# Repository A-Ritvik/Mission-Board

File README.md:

# The Mission Board
The mission board is a robotics control board with space for up to 8 motors and 4 servos featuring both ESP32 and RP2040 processors at its core. It also has a display to achieve easier debugging and customization. Sensors include a gyro, accelerometer, and magnetometer. 

# 3D Renders/Images
With Case (PS. Image is slightly off)-

PCB -

# Full Feature List

- Gyro, Accelerometer, Magnetometer
- Up to 4 servos
- Up to 8 motors
- Display connector
- 2 USB for programming RP2040 and ESP32 (no power functionality)
- 1 Barrel Jack for power
- Debug Lights + 5 Customizable Switches

# Case

The case uses a bottom and top part; the bottom part holds the pcb while the top part holds the display. The top part is removable and uses 2 4M screws to attach, and the bottom part needs 3 6M screws to attach to the PCB. 

# Schematic & PCB

# Bill of Materials

The full BOM can be found under the productions folder in CSV format. The total comes to around 132.22$ to produce the board.

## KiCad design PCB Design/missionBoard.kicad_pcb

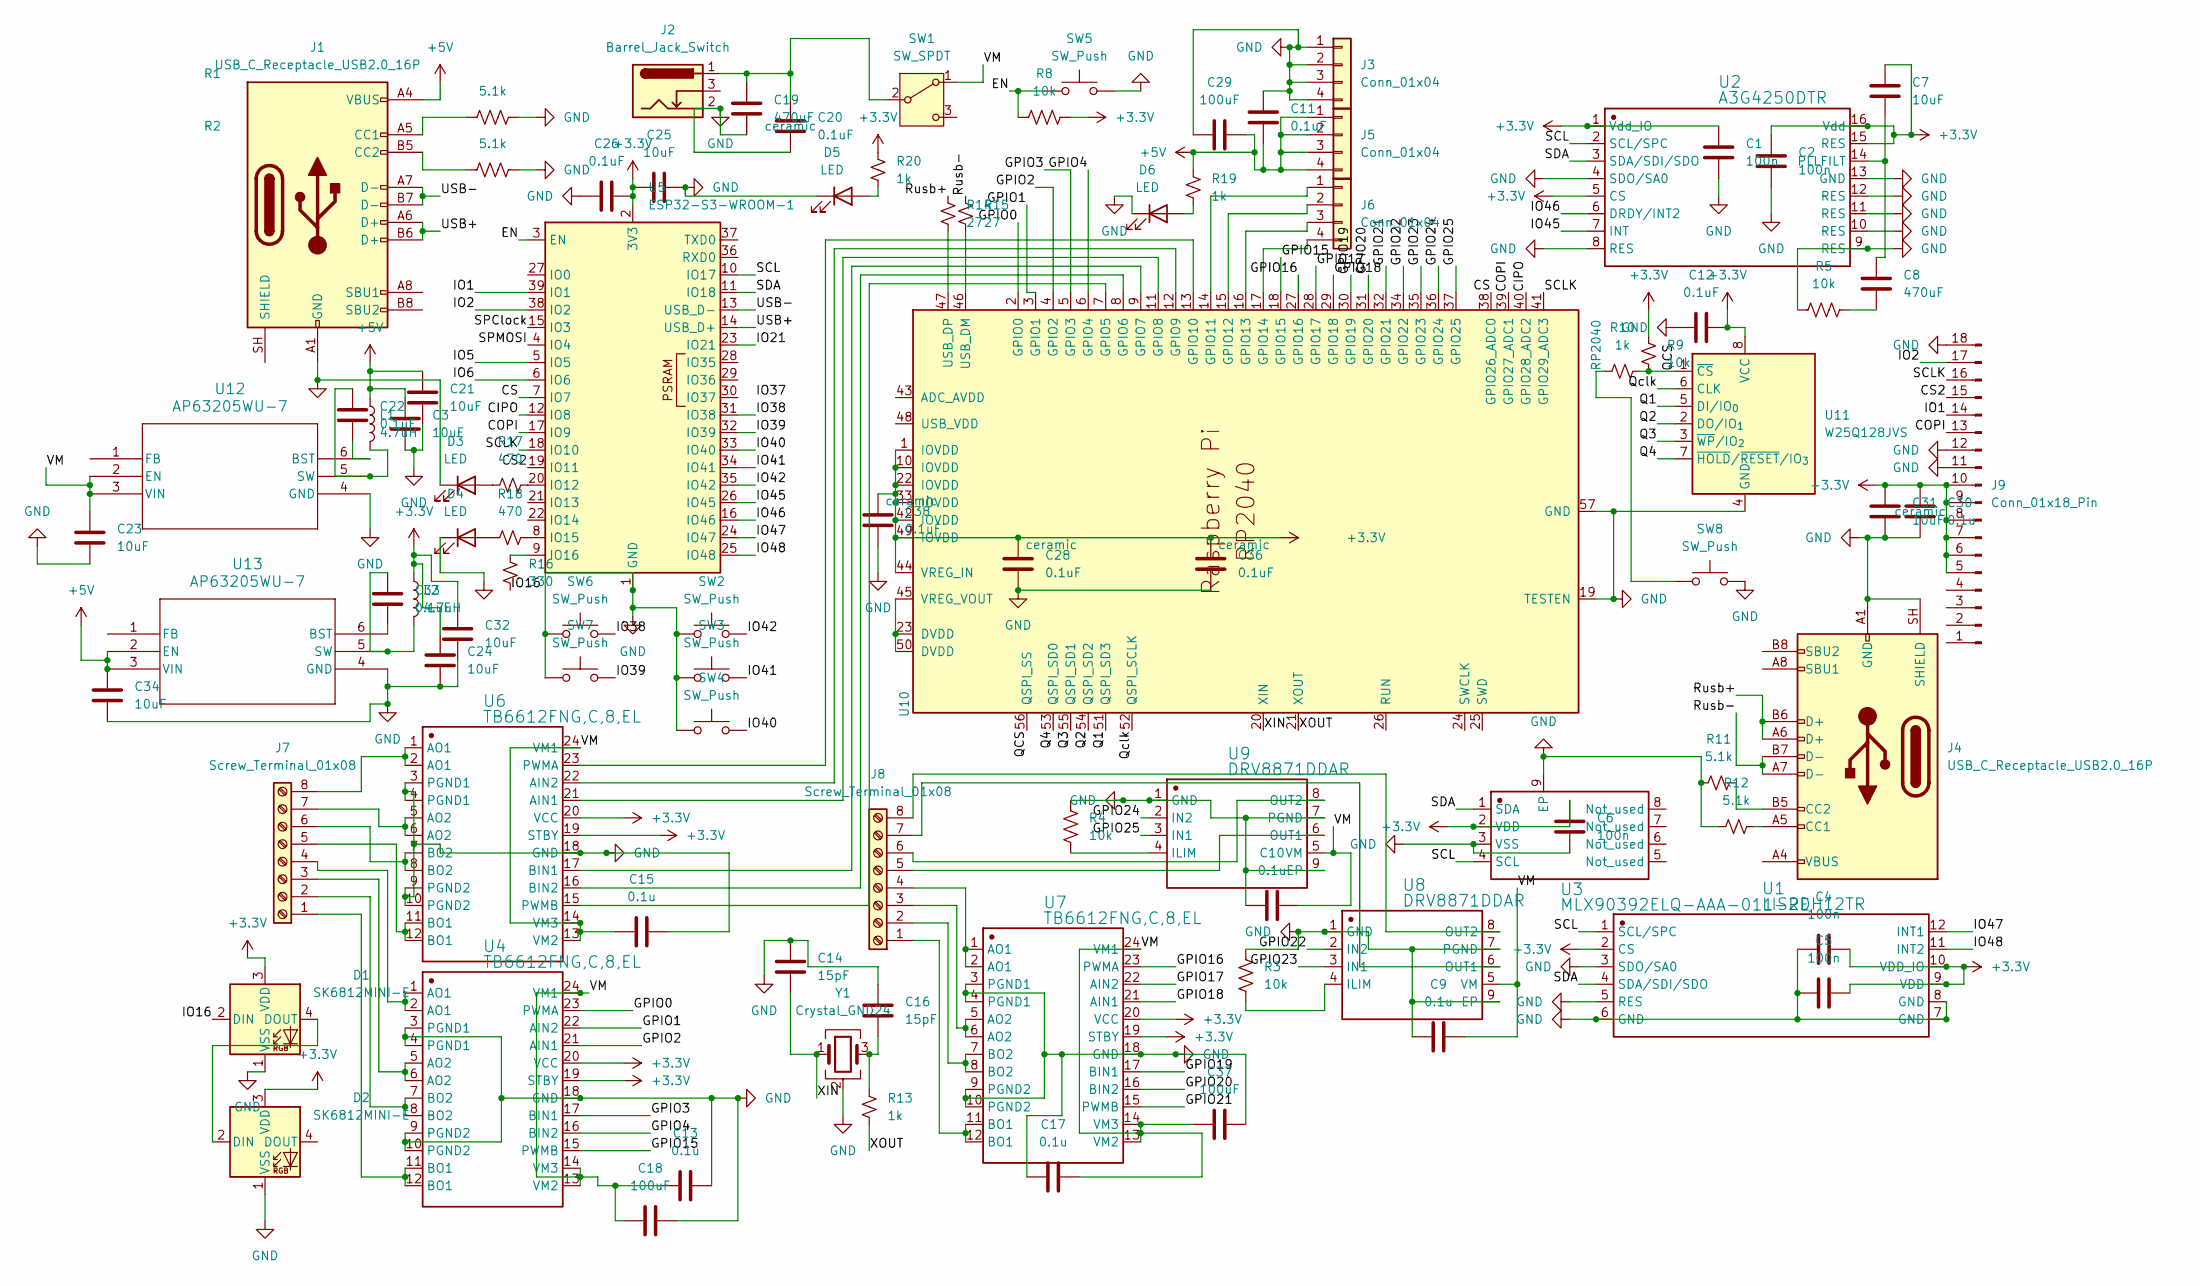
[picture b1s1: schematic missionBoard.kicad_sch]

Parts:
C1, C2, C4, C5, C6: 100n; C_0402_1005Metric
C3, C7, C21, C23, C24, C25, C31, C32, C34: 10uF; C_0402_1005Metric
C8, C19: 470uF; C_Elec_10x10.2
C9, C10, C13, C15, C17, C30: 0.1u; C_0402_1005Metric
C11, C12, C20, C22, C26, C28, C33, C36, C38: 0.1uF; C_0402_1005Metric
C14, C16: 15pF; C_0603_1608Metric
C18, C29, C37: 100uF; C_Elec_6.3x7.7
D1, D2: SK6812MINI-E; LED_SK6812MINI-E_3.2x2.8mm_P1.5mm_ReverseMount
D3, D4, D5, D6: LED; LED_0603_1608Metric
J1, J4: USB_C_Receptacle_USB2.0_16P; USB_C_Receptacle_HCTL_HC-TYPE-C-16P-01A
J2: Barrel_Jack_Switch; BarrelJack_Kycon_KLDX-0202-xC_Horizontal
J3, J5, J6: Conn_01x04; PinHeader_1x04_P2.54mm_Vertical
J7, J8: Screw_Terminal_01x08; TerminalBlock_Phoenix_MKDS-3-8-5.08_1x08_P5.08mm_Horizontal
J9: Conn_01x18_Pin; Hirose_FH12-18S-0.5SH_1x18-1MP_P0.50mm_Horizontal
L1, L2: 4.7uH; L_APV_ANR4030
R1, R2, R11, R12: 5.1k; R_0402_1005Metric
R3, R4, R5, R8, R9: 10k; R_0402_1005Metric
R10, R13: 1k; R_0402_1005Metric
R14, R15: 27; R_0402_1005Metric
R16: 330; R_0603_1608Metric
R17, R18: 470; R_0603_1608Metric
R19, R20: 1k; R_0603_1608Metric
SW1: SW_SPDT; SW_SPDT_Shouhan_MSK12C02
SW2, SW3, SW4, SW6, SW7: SW_Push; SW_SPST_SKQG_WithoutStem
SW5, SW8: SW_Push; SW_Push_SPST_NO_Alps_SKRK
U1: LIS2DH12TR; SENSOR_LIS2DH12; Manufacturer Part LIS2DH12TR
U2: A3G4250DTR; Manufacturer Part A3G4250DTR
U3: MLX90392ELQ-AAA-011-RE; UTDFN-8 2x2.5_MEL; Manufacturer Part MLX90392ELQ-AAA-011-RE
U4, U6, U7: TB6612FNG,C,8,EL; SOP65P760X160-24N; Manufacturer Part TB6612FNG,C,8,EL
U5: ESP32-S3-WROOM-1
U8, U9: DRV8871DDAR; VREG_LM5017MR_NOPB; Manufacturer Part DRV8871DDAR
U10: RP2040; RP2040-QFN-56
U11: W25Q128JVS; SOIC-8_5.3x5.3mm_P1.27mm
U12, U13: AP63205WU-7; SOIC_05WU-7_DIO
Y1: Crystal_GND24; Crystal_SMD_3225-4Pin_3.2x2.5mm

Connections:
+3.3V: C1.1, C2.1, C4.2, C5.2, C6.1, C7.1, C12.1, C24.1, C25.1, C26.2, C28.2, C30.1, C31.2, C32.1, C36.2, C38.2, D1.3 (VDD), D2.3 (VDD), J9.5, J9.6, J9.7, J9.8, J9.9, J9.10, L2.1, R8.2, R9.1, R20.1, U1.2 (CS), U1.9 (VDD), U1.10 (VDD_IO), U2.1 (Vdd_IO), U2.5 (CS), U2.15 (RES), U2.16 (Vdd), U3.2 (VDD), U4.19 (STBY), U4.20 (VCC), U5.2 (3V3), U6.19 (STBY), U6.20 (VCC), U7.19 (STBY), U7.20 (VCC), U10.1 (IOVDD), U10.10 (IOVDD), U10.22 (IOVDD), U10.33 (IOVDD), U10.42 (IOVDD), U10.44 (VREG_IN), U10.49 (IOVDD), U11.8 (VCC)
+5V: C3.1, C11.2, C21.1, C29.1, C34.1, J1.A4 (VBUS), J1.A9 (VBUS), J1.B4 (VBUS), J1.B9 (VBUS), J5.1, J5.2, J5.3, J5.4, L1.1, R19.1, U13.2 (EN), U13.3 (VIN)
/CIPO: U5.12 (IO8), U10.40 (GPIO28_ADC2)
/COPI: J9.13, U5.17 (IO9), U10.39 (GPIO27_ADC1)
/CS: U5.7 (IO7), U10.38 (GPIO26_ADC0)
/CS2: J9.15, U5.19 (IO11)
/EN: R8.1, SW5.1, U5.3 (EN)
/GPIO0: U4.23 (PWMA), U10.2 (GPIO0)
/GPIO1: U4.22 (AIN2), U10.3 (GPIO1)
/GPIO2: U4.21 (AIN1), U10.4 (GPIO2)
/GPIO3: U4.17 (BIN1), U10.5 (GPIO3)
/GPIO4: U4.16 (BIN2), U10.6 (GPIO4)
/GPIO15: U4.15 (PWMB), U10.18 (GPIO15)
/GPIO16: U7.23 (PWMA), U10.27 (GPIO16)
/GPIO17: U7.22 (AIN2), U10.28 (GPIO17)
/GPIO18: U7.21 (AIN1), U10.29 (GPIO18)
/GPIO19: U7.17 (BIN1), U10.30 (GPIO19)
/GPIO20: U7.16 (BIN2), U10.31 (GPIO20)
/GPIO21: U7.15 (PWMB), U10.32 (GPIO21)
/GPIO22: U8.2 (IN2), U10.34 (GPIO22)
/GPIO23: U8.3 (IN1), U10.35 (GPIO23)
/GPIO24: U9.2 (IN2), U10.36 (GPIO24)
/GPIO25: U9.3 (IN1), U10.37 (GPIO25)
/IO1: J9.14, U5.39 (IO1)
/IO2: J9.17, U5.38 (IO2)
/IO5: U5.5 (IO5)
/IO6: U5.6 (IO6)
/IO16: D1.2 (DIN), R16.2
/IO21: U5.23 (IO21)
/IO38: SW6.2, U5.31 (IO38)
/IO39: SW7.2, U5.32 (IO39)
/IO40: SW4.2, U5.33 (IO40)
/IO41: SW3.2, U5.34 (IO41)
/IO42: SW2.2, U5.35 (IO42)
/IO45: U2.7 (INT), U5.26 (IO45)
/IO46: U2.6 (DRDY/INT2), U5.16 (IO46)
/IO47: U1.12 (INT1), U5.24 (IO47)
/IO48: U1.11 (INT2), U5.25 (IO48)
/Q1: U10.51 (QSPI_SD3), U11.5 (DI/IO_{0})
/Q2: U10.54 (QSPI_SD2), U11.2 (DO/IO_{1})
/Q3: U10.55 (QSPI_SD1), U11.3 (~WP/IO_{2})
/Q4: U10.53 (QSPI_SD0), U11.7 (~HOLD/~RESET/IO_{3})
/QCS: R9.2, R10.2, U10.56 (QSPI_SS), U11.1 (~CS)
/Qclk: U10.52 (QSPI_SCLK), U11.6 (CLK)
/Rusb+: J4.A6 (D+), J4.B6 (D+), R14.1
/Rusb-: J4.A7 (D-), J4.B7 (D-), R15.1
/SCL: U1.1 (SCL/SPC), U2.2 (SCL/SPC), U3.4 (SCL), U5.10 (IO17)
/SCLK: J9.16, U5.18 (IO10), U10.41 (GPIO29_ADC3)
/SDA: U1.4 (SDA/SDI/SDO), U2.3 (SDA/SDI/SDO), U3.1 (SDA), U5.11 (IO18)
/SPClock: U5.15 (IO3)
/SPMOSI: U5.4 (IO4)
/USB+: J1.A6 (D+), J1.B6 (D+), U5.14 (USB_D+)
/USB-: J1.A7 (D-), J1.B7 (D-), U5.13 (USB_D-)
/VM: C9.1, C10.1, C13.2, C15.2, C17.1, C18.1, C23.1, C37.1, SW1.1 (A), U4.13 (VM2), U4.14 (VM3), U4.24 (VM1), U6.13 (VM2), U6.14 (VM3), U6.24 (VM1), U7.13 (VM2), U7.14 (VM3), U7.24 (VM1), U8.5 (VM), U9.5 (VM), U12.2 (EN), U12.3 (VIN)
/XIN: C14.2, U10.20 (XIN), Y1.1
/XOUT: R13.2, U10.21 (XOUT)
GND: C1.2, C2.2, C3.2, C4.1, C5.1, C6.2, C9.2, C10.2, C11.1, C12.2, C13.1, C14.1, C15.1, C16.1, C17.2, C18.2, C19.2, C20.1, C21.2, C23.2, C24.2, C25.2, C26.1, C28.1, C29.2, C30.2, C31.1, C32.2, C34.2, C36.1, C37.2, C38.1, D1.1 (VSS), D2.1 (VSS), D3.1 (K), D4.1 (K), D5.1 (K), D6.1 (K), J1.A1 (GND), J1.A12 (GND), J1.B1 (GND), J1.B12 (GND), J2.2, J3.1, J3.2, J3.3, J3.4, J4.A1 (GND), J4.A12 (GND), J4.B1 (GND), J4.B12 (GND), J4.SH (SHIELD), J9.11, J9.12, J9.18, R1.2, R2.2, R3.2, R4.2, R5.1, R11.1, R12.1, SW2.1, SW3.1, SW4.1, SW5.2, SW6.1, SW7.1, SW8.2, U1.3 (SDO/SA0), U1.5 (RES), U1.6 (GND), U1.7 (GND), U1.8 (GND), U2.4 (SDO/SA0), U2.8 (RES), U2.9 (RES), U2.10 (RES), U2.11 (RES), U2.12 (RES), U2.13 (GND), U3.3 (VSS), U3.9 (EP), U4.3 (PGND1), U4.4 (PGND1), U4.9 (PGND2), U4.10 (PGND2), U4.18 (GND), U5.1 (GND), U5.40 (GND), U5.41 (GND), U6.3 (PGND1), U6.4 (PGND1), U6.9 (PGND2), U6.10 (PGND2), U6.18 (GND), U7.3 (PGND1), U7.4 (PGND1), U7.9 (PGND2), U7.10 (PGND2), U7.18 (GND), U8.1 (GND), U8.7 (PGND), U8.9 (EP), U9.1 (GND), U9.7 (PGND), U9.9 (EP), U10.19 (TESTEN), U10.57 (GND), U11.4 (GND), U12.4 (GND), U13.4 (GND), Y1.2 (G), Y1.4 (G)
unnamed: C8.2, R5.2
unnamed: C16.2, R13.1, Y1.3
unnamed: D1.4 (DOUT), D2.2 (DIN)
unnamed: D3.2 (A), R17.1
unnamed: D4.2 (A), R18.1
unnamed: D5.2 (A), R20.2
unnamed: D6.2 (A), R19.2
unnamed: J1.A5 (CC1), R1.1
unnamed: J1.B5 (CC2), R2.1
unnamed: J4.A5 (CC1), R12.2
unnamed: J4.B5 (CC2), R11.2
unnamed: J4.A4 (VBUS), J4.A9 (VBUS), J4.B4 (VBUS), J4.B9 (VBUS)
unnamed: J6.1, U10.14 (GPIO11)
unnamed: J6.2, U10.15 (GPIO12)
unnamed: J6.3, U10.16 (GPIO13)
unnamed: J6.4, U10.17 (GPIO14)
unnamed: J7.1, U4.11 (BO1), U4.12 (BO1)
unnamed: J7.2, U4.7 (BO2), U4.8 (BO2)
unnamed: J7.3, U4.5 (AO2), U4.6 (AO2)
unnamed: J7.4, U4.1 (AO1), U4.2 (AO1)
unnamed: J7.5, U6.11 (BO1), U6.12 (BO1)
unnamed: J7.6, U6.7 (BO2), U6.8 (BO2)
unnamed: J7.7, U6.5 (AO2), U6.6 (AO2)
unnamed: J7.8, U6.1 (AO1), U6.2 (AO1)
unnamed: J8.1, U7.11 (BO1), U7.12 (BO1)
unnamed: J8.2, U7.7 (BO2), U7.8 (BO2)
unnamed: J8.3, U7.5 (AO2), U7.6 (AO2)
unnamed: J8.4, U7.1 (AO1), U7.2 (AO1)
unnamed: J8.5, U9.6 (OUT1)
unnamed: J8.6, U9.8 (OUT2)
unnamed: J8.7, U8.6 (OUT1)
unnamed: J8.8, U8.8 (OUT2)
unnamed: R10.1, SW8.1
unnamed: C19.1, C20.2, J2.1, SW1.2 (B)
unnamed: C7.2, C8.1, U2.14 (PLLFILT)
unnamed: R17.2, U5.20 (IO12)
unnamed: R18.2, U5.8 (IO15)
unnamed: R16.1, U5.9 (IO16)
unnamed: R3.1, U8.4 (ILIM)
unnamed: R4.1, U9.4 (ILIM)
unnamed: U6.15 (PWMB), U10.7 (GPIO5)
unnamed: U6.16 (BIN2), U10.8 (GPIO6)
unnamed: U6.17 (BIN1), U10.9 (GPIO7)
unnamed: U6.21 (AIN1), U10.11 (GPIO8)
unnamed: U6.22 (AIN2), U10.12 (GPIO9)
unnamed: U6.23 (PWMA), U10.13 (GPIO10)
unnamed: R15.2, U10.46 (USB_DM)
unnamed: R14.2, U10.47 (USB_DP)
unnamed: U10.23 (DVDD), U10.45 (VREG_VOUT), U10.50 (DVDD)
unnamed: C22.2, U12.6 (BST)
unnamed: C22.1, L1.2, U12.5 (SW)
unnamed: C33.2, U13.6 (BST)
unnamed: C33.1, L2.2, U13.5 (SW)

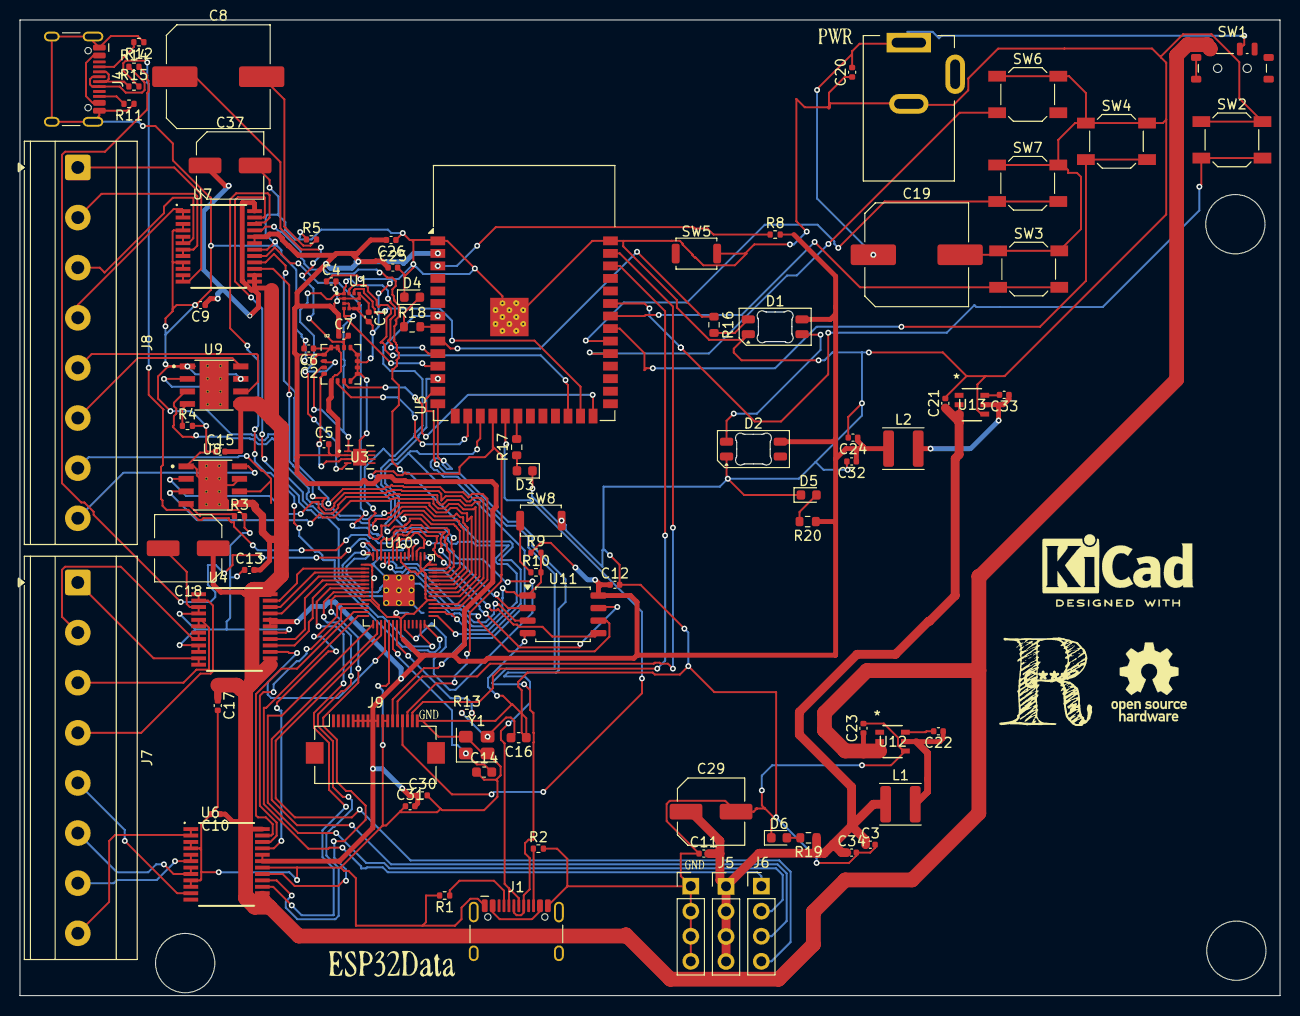
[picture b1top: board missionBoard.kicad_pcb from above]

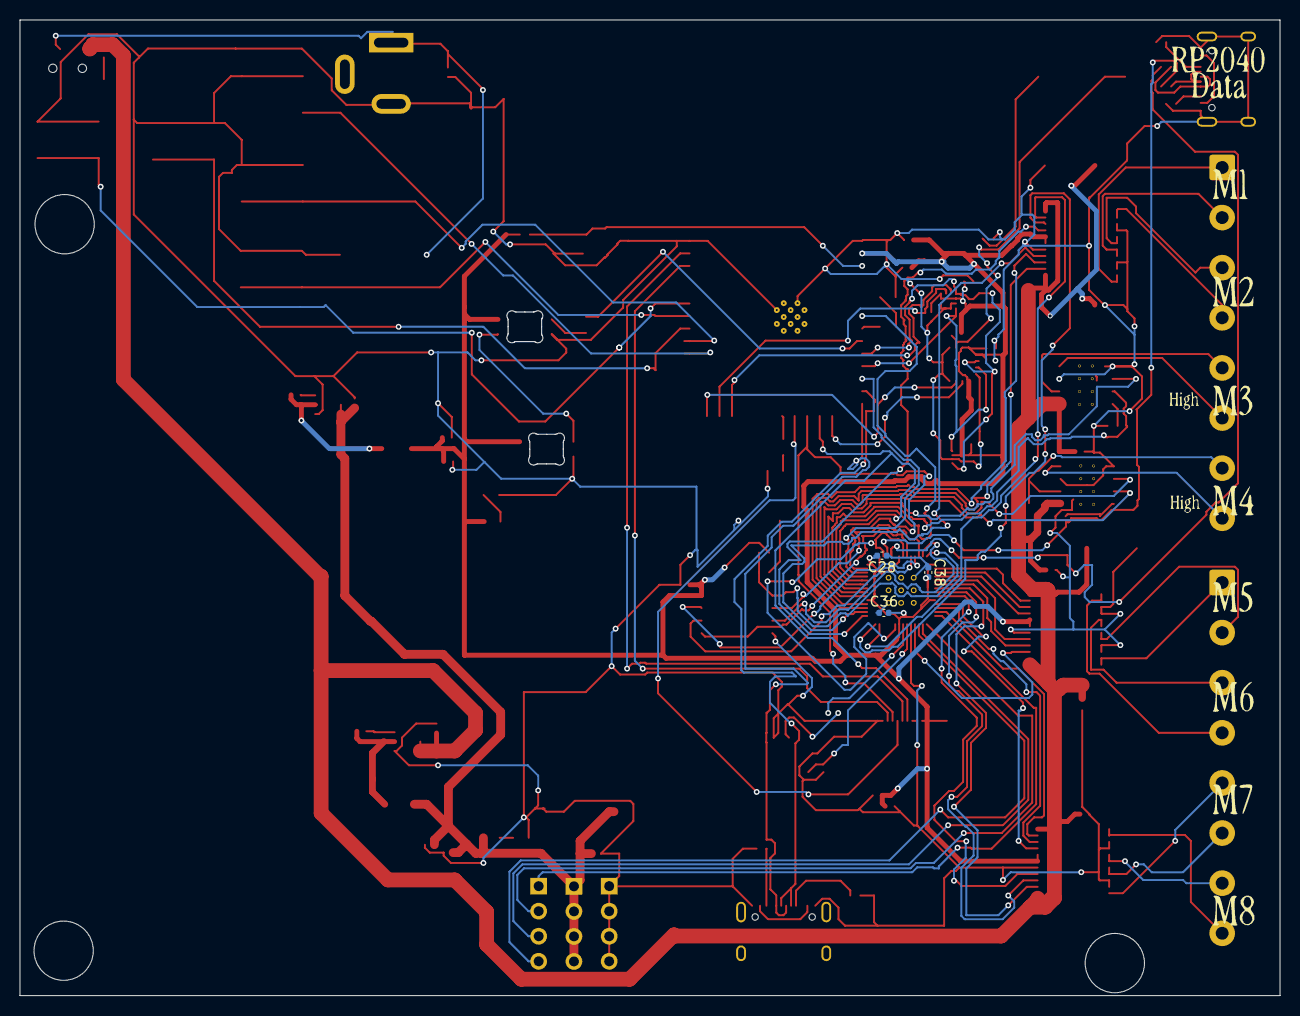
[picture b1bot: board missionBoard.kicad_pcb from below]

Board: 2 copper layers, 127.7 x 98.9 mm, 93 parts (3 on the bottom side), 105 nets.

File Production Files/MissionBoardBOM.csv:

,Designator,Footprint,Quantity,Designation,Supplier Link,Cost
,"C1, C2, C4, C5, C6, C3, C7, C21, C23, C24, C32, C34, C9, C10, C11, C12, C22, C33",C_0402_1005Metric,18,100n,TORCH CC0402X7R25V104KN,$1.42
,"C8, C19, C27",C_Elec_10x10.2,2,470uF,ROQANG RVT1V471M1010 ,$0.42
,"C14, C16",C_0603_1608Metric,2,15pF,YAGEO CC0603FRNPO9BN150 ,$1.28
,"C18, C29, C37",C_Elec_6.3x7.7,3,100uF,ROQANG RVT1V101M0607 ,$0.65
,"C3, C7, C21, C23, C24, C25, C31, C32, C34",C_0402_1005Metric,9,10uF,muRata GRM155R61A106ME11D,$0.87
,"D1, D2",LED_SK6812MINI-E_3.2x2.8mm_P1.5mm_ReverseMount,2,SK6812MINI-E,OPSCO Optoelectronics SK6812MINI-E ,$0.44
,"D3, D4, D5, D6",LED_0603_1608Metric,4,LED,YONGYUTAI YLED0603B ,$0.58
,"J1, J4",USB_C_Receptacle_HCTL_HC-TYPE-C-16P-01A,2,USB_C_Receptacle_USB2.0_16P,SHOU HAN TYPE-C 16P QTWT ,$0.41
,J2,BarrelJack_Kycon_KLDX-0202-xC_Horizontal,1,Barrel_Jack_Switch,KLDX-0202-A ,$0.77
,"J3, J5, J6",PinHeader_1x04_P2.54mm_Vertical,3,Conn_01x04,hanxia HX PH254-01-04-Z-L11.5 straight pin header ,$0.57
,"J7, J8",TerminalBlock_Phoenix_MKDS-3-8-5.08_1x08_P5.08mm_Horizontal,8,Screw_Terminal_01x02,"Phoenix Contact MKDS 1,5/ 2-5,08 ",$3.97
,J9,Hirose_FH12-18S-0.5SH_1x18-1MP_P0.50mm_Horizontal,1,Conn_01x18_Pin,HRS FH12-18S-0.5SH(55),$0.68
,"L1, L2",L_6.3x6.3_H3,2,4.7uH,APV ANR4030T4R7M ,$0.44
,"R1, R2, R11, R12",R_0402_1005Metric,4,5.1k,FOJAN FRC0402J512 TS ,$0.25
,"R3, R4, R5, R8, R9",R_0402_1005Metric,5,10k,VISHAY CRCW040210K0FKED ,$0.25
,"R10, R13",R_0402_1005Metric,2,1k,YAGEO RT0402BRE071KL ,$0.50
,"R14, R15",R_0402_1005Metric,2,27k,YAGEO RP0402BRD0727KL ,$0.43
,R16,R_0603_1608Metric,1,330k,FOJAN FRC0603J334 TS ,$0.22
,"R17, R18",R_0603_1608Metric,2,470k,FOJAN FRC0603F4703TS ,$0.29
,"R19, R20",R_0603_1608Metric,2,1k,YAGEO RT0603BRD071KL ,$0.59
,SW1,SW_SPDT_Shouhan_MSK12C02,1,SW_SPDT,SHOU HAN MSK12C02 ,$0.58
,"SW2, SW3, SW4, SW6, SW7",SW_SPST_SKQG_WithoutStem,5,SW_Push,ALPSALPINE SKQGABE010 ,$0.57
,"SW5, SW8",SW_Push_SPST_NO_Alps_SKRK,2,SW_Push,ALPSALPINE SKRKAEE020 ,$0.67
,U1,SENSOR_LIS2DH12,1,LIS2DH12TR,ST LIS2DH12TR ,$0.92
,U2,A3G4250DTR,1,A3G4250DTR,ST A3G4250DTR ,$1.84
,U3,UTDFN-8 2x2.5_MEL,1,MLX90392ELQ-AAA-011-RE,Melexis MLX90392ELQ-AAA-011-RE ,$1.84
,"U4, U6, U7",SOP65P760X160-24N,3,"TB6612FNG,C,8,EL","TOSHIBA TB6612FNG,C,8,EL ",$3.38
,U5,ESP32-S3-WROOM-1,1,ESP32-S3-WROOM-1,ESPRESSIF ESP32-S3-WROOM-1-N4 ,$4.66
,"U8, U9",VREG_LM5017MR_NOPB,2,DRV8871DDAR,TI DRV8871DDAR ,$5.21
,U10,RP2040-QFN-56,1,RP2040,Raspberry Pi RP2040 ,$0.99
,U11,SOIC-8_5.3x5.3mm_P1.27mm,1,W25Q128JVS,Winbond W25Q128JVSIQ ,$3.18
,"U12, ",SOIC_05WU-7_DIO,1,AP63205WU-7,DIODES AP63205WU-7 ,$0.44
,U13,SOIC_05WU-7_DIO,1,AP63203WU-7,DIODES AP63203WU-7 ,$0.62
,Y1,Crystal_SMD_3225-4Pin_3.2x2.5mm,1,Crystal_GND24,YXC Crystal Oscillators X322512MSB4SI ,$0.50
,PCB,n/a,1,n/a,jlcpcb.com,$28.00
,Display,n/a,1,HS280S030RX,HS280S030RX ,$4.93
,Soldering Iron,n/a,1,n/a,Soldering Iron ,$15.95
,Flux Paste,n/a,1,n/a,Flux Paste ,$5.95
,Solder,n/a,1,n/a,Solder ,$9.99
,M6 Screws,n/a,1,n/a,M6 Screws ,$5.99
,Amazon Shipping,,1,,amazon.com ,$0.00
,Digikey Shipping(+tarrif),n/a,1,n/a,digikey.com,$8.85
,LCSC Shipping,n/a,1,n/a,lcsc.com,$12.13
,Total Cost,PS. Some of these prices may have changed,,,,132.22
